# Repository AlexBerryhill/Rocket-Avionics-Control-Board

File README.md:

# Rocket Avionics Control Board
 Skys the Limit

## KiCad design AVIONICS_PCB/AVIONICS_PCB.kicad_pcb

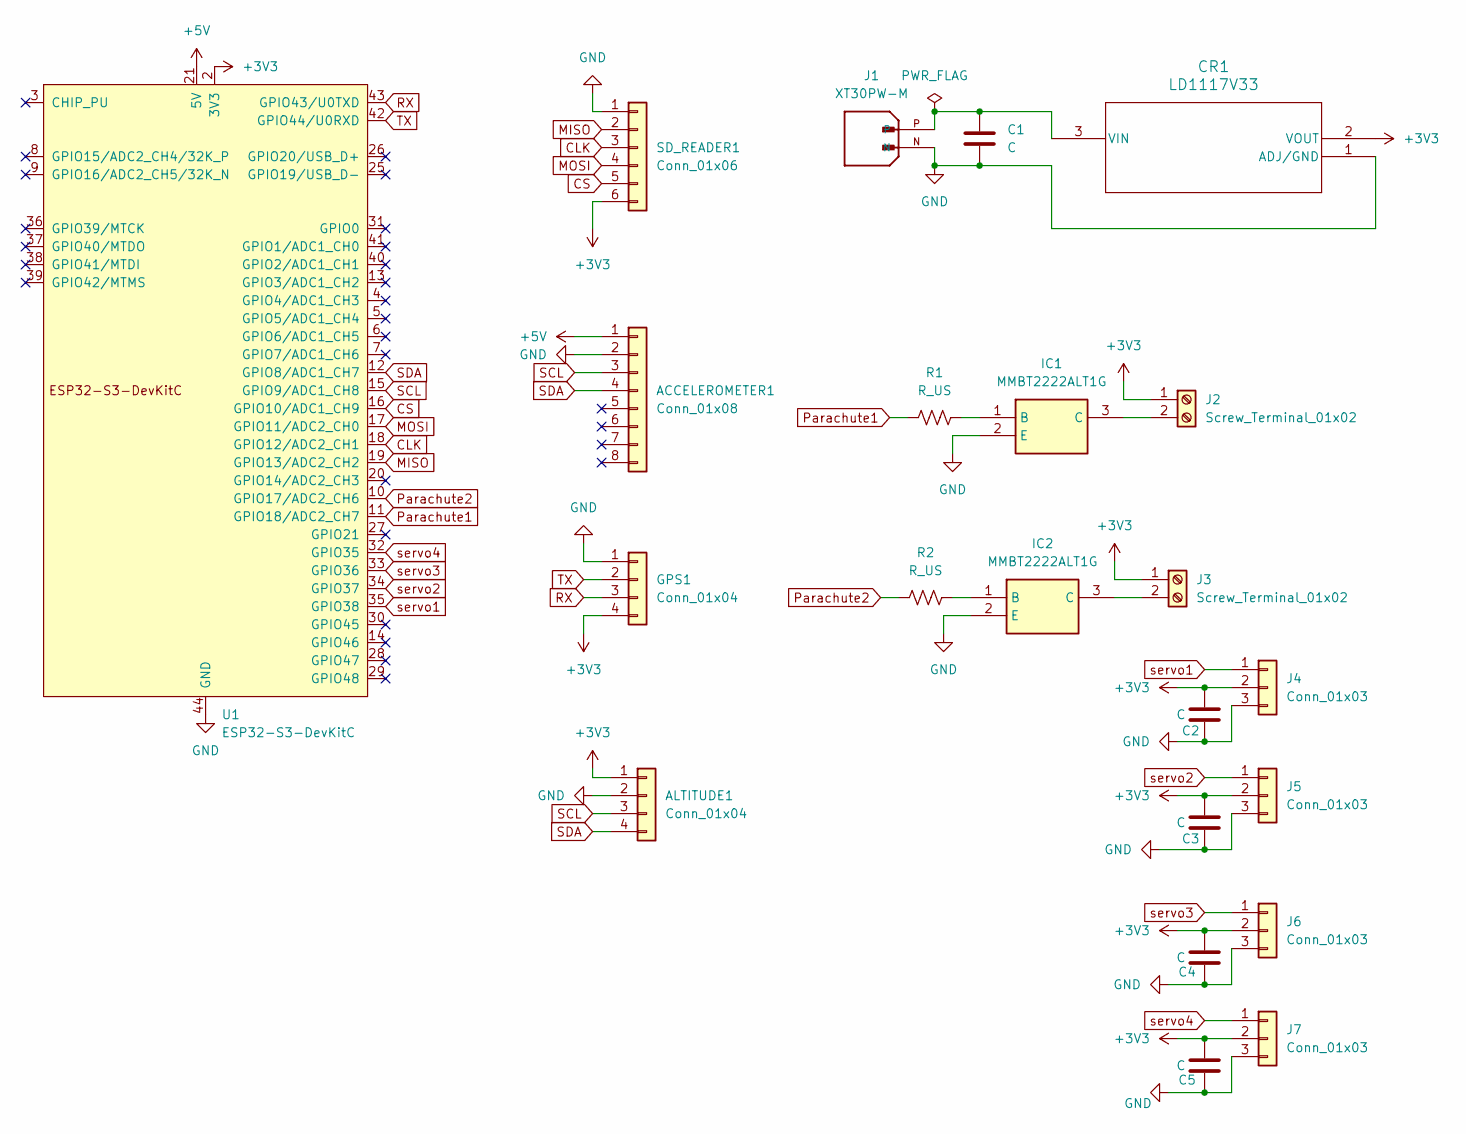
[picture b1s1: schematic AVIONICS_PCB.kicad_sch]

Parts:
ACCELEROMETER1: Conn_01x08; PinHeader_1x08_P2.54mm_Vertical
ALTITUDE1: Conn_01x04; PinHeader_1x04_P2.54mm_Vertical
C1, C2, C3, C4, C5: C; C_0805_2012Metric_Pad1.18x1.45mm_HandSolder
CR1: LD1117V33; TO-220_STM
GPS1: Conn_01x04; PinHeader_1x04_P2.54mm_Vertical
IC1, IC2: MMBT2222ALT1G; SOT96P237X111-3N; Manufacturer_Part_Number MMBT2222ALT1G
J1: XT30PW-M; AMASS_XT30PW-M; PARTREV 1.2
J2, J3: Screw_Terminal_01x02; TerminalBlock_Phoenix_MPT-0,5-2-2.54_1x02_P2.54mm_Horizontal
J4, J5, J6, J7: Conn_01x03; Molex_KK-254_AE-6410-03A_1x03_P2.54mm_Vertical
R1, R2: R_US; R_1206_3216Metric_Pad1.30x1.75mm_HandSolder
SD_READER1: Conn_01x06; PinHeader_1x06_P2.54mm_Vertical
U1: ESP32-S3-DevKitC

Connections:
+3V3: ALTITUDE1.1, C2.1, C3.1, C4.1, C5.1, CR1.2 (VOUT), GPS1.4, J2.1, J3.1, J4.2, J5.2, J6.2, J7.2, SD_READER1.6, U1.1 (3V3), U1.2 (3V3)
+5V: ACCELEROMETER1.1, U1.21 (5V)
CLK: SD_READER1.3, U1.18 (GPIO12/ADC2_CH1)
CS: SD_READER1.5, U1.16 (GPIO10/ADC1_CH9)
GND: ACCELEROMETER1.2, ALTITUDE1.2, C1.2, C2.2, C3.2, C4.2, C5.2, CR1.1 (ADJ/GND), GPS1.1, IC1.2 (E), IC2.2 (E), J1.N, J1.S1, J1.S2, J4.3, J5.3, J6.3, J7.3, SD_READER1.1, U1.22 (GND), U1.23 (GND), U1.24 (GND), U1.44 (GND)
MISO: SD_READER1.2, U1.19 (GPIO13/ADC2_CH2)
MOSI: SD_READER1.4, U1.17 (GPIO11/ADC2_CH0)
unnamed: C1.1, CR1.3 (VIN), J1.P
unnamed: IC1.1 (B), R1.2
unnamed: IC1.3 (C), J2.2
unnamed: IC2.1 (B), R2.2
unnamed: IC2.3 (C), J3.2
Parachute1: R1.1, U1.11 (GPIO18/ADC2_CH7)
Parachute2: R2.1, U1.10 (GPIO17/ADC2_CH6)
RX: GPS1.3, U1.43 (GPIO43/U0TXD)
SCL: ACCELEROMETER1.3, ALTITUDE1.3, U1.15 (GPIO9/ADC1_CH8)
SDA: ACCELEROMETER1.4, ALTITUDE1.4, U1.12 (GPIO8/ADC1_CH7)
TX: GPS1.2, U1.42 (GPIO44/U0RXD)
servo1: J4.1, U1.35 (GPIO38)
servo2: J5.1, U1.34 (GPIO37)
servo3: J6.1, U1.33 (GPIO36)
servo4: J7.1, U1.32 (GPIO35)

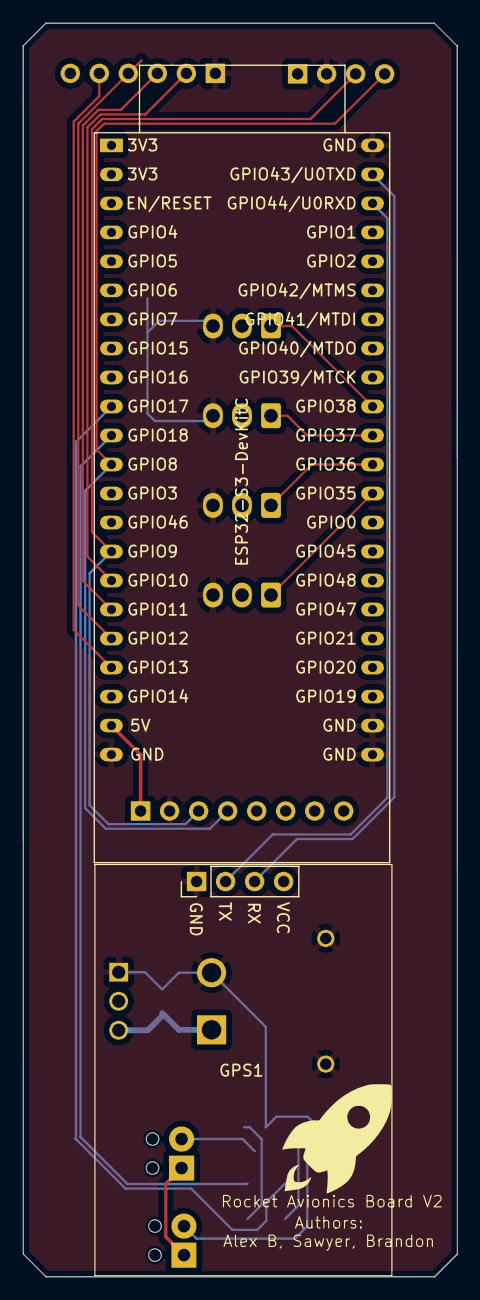
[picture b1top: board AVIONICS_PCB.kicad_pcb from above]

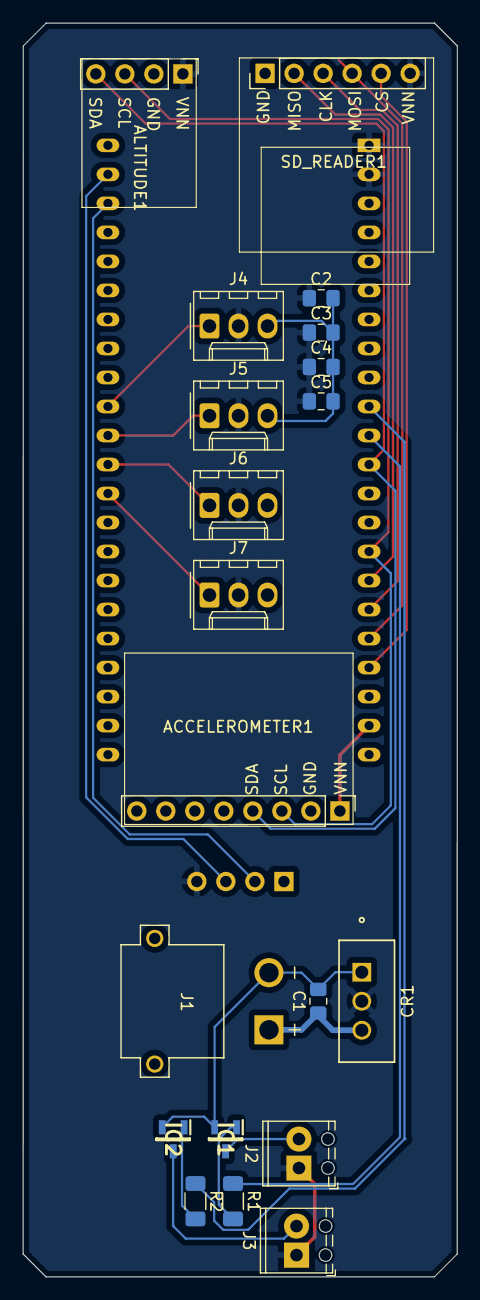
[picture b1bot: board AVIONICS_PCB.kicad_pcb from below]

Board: 2 copper layers, 38.0 x 109.8 mm, 22 parts (20 on the bottom side), 22 nets.

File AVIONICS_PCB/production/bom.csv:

Designator,Footprint,Quantity,Value,LCSC Part #
ACCELEROMETER,PinHeader_1x08_P2.54mm_Vertical,1,Conn_01x08,
"ALTITUDE, GPS",PinHeader_1x04_P2.54mm_Vertical,2,Conn_01x04,
"C1, C2, C3, C4, C5",0805,5,C,
CR1,TO-220_STM,1,LD1117V33,
"IC1, IC2",SOT96P237X111-3N,2,MMBT2222ALT1G,
J1,AMASS_XT30PW-M,1,XT30PW-M,
"J2, J3","TerminalBlock_Phoenix_MPT-0,5-2-2.54_1x02_P2.54mm_Horizontal",2,Screw_Terminal_01x02,
"J4, J5, J6, J7",Molex_KK-254_AE-6410-03A_1x03_P2.54mm_Vertical,4,Conn_01x03,
"R1, R2",1206,2,R_US,
SD_READER,PinHeader_1x06_P2.54mm_Vertical,1,Conn_01x06,
U1,ESP32-S3-DevKitC,1,ESP32-S3-DevKitC,

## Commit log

2025-01-27 Initialized PIO
2025-01-31 Added libraries
2025-01-31 Created framework
2025-02-03 Built skeleton
2025-02-06 Started GPS and Finished multiprocessing
2025-02-19 changes to schematic
2025-02-20 Updated board
2025-02-20 Started footprint layout
2025-02-20 Started layout
2025-02-24 got arduino working, now on to pio
2025-02-25 Added power system
2025-02-25 Platformio is now ready
2025-02-26 Got sensors in right configuration
2025-02-27 lab8
2025-02-28 Compact the board
2025-03-01 add gyro to main
2025-03-05 Servos
    Updated the schematic to include circuitry for the servos
2025-03-05 production v1.0
2025-03-05 NPN Transistor
2025-03-06 Board v2
2025-03-07 autosave
2025-03-19 SD testing
2025-03-24 added SD card
2025-03-26 reading and saving 6dof and alt to SD
2025-03-26 CSV format ant visualizer
2025-03-31 New servo code (In Progress)
2025-03-31 New Chnaged (in progress)
2025-03-31 who knows what this is
2025-03-31 New code (In Progress)
2025-03-31 Class Changes (in progress)
2025-03-31 Code Should "Work"
2025-04-01 GPS
    Added GPS
2025-04-01 Added servo library
2025-04-01 Working
2025-04-01 Working with ESP_NOW
2025-04-02 IT wasnt me
2025-04-02 Added live telemetry sending
2025-04-02 Updated stack size
2025-04-02 Started on motor work
2025-04-03 It's working
2025-04-07 working on v3
